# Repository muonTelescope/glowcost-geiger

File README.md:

# gLowCost-geiger

**Simple description:** this is a compact four-wire Geiger module for a Raspberry
Pi. It powers a CTC-5 / STS-5 tube from 3.3 V, generates the tube's high voltage,
and exposes raw TTL pulses plus a future STEMMA QT I²C telemetry interface.
The ATtiny1616 is the production logic device: it counts pulses, serves I2C diagnostics, reads address straps, and reports HV/3V3 telemetry without changing the raw hardware pulse path.

> **Prototype:** the KiCad routing has known DRC clearance errors. The HV design
> is not bench-qualified or approved for fabrication. Use suitable HV procedures.

## Design summary

- Hardware HV oscillator, switch, multiplier, protection, and comparator.
- TTL pulse output plus green 0805 pulse LED with cuttable enable bridge.
- Horizontal CTC-5 / STS-5 tube under two DNP C142864 clips.
- Two STEMMA QT / SparkFun Qwiic connectors in parallel for I²C daisy chaining.
- ATtiny1616 option for pulse counting, HV/3.3 V readback, fault flags, and I²C slave registers.
- Two solder-selectable address pads on leftover MCU GPIOs.
- 120 x 32 x 1.6 mm, two-layer compact PCB.
- Two 1.0 mm routed Edge.Cuts isolation slots split the HV service region.

## STEMMA QT and address selection

STEMMA QT and Qwiic use the same JST-SH 4-pin bus: GND, 3.3 V, SDA, and SCL.
The two connectors are parallel pass-through ports. Enable only one pull-up set on
each bus segment.

Address links are two-pad bridges. Open is logic-high through the ATtiny1616
internal pull-up; bridged is logic-low:

| A1 | A0 | Address |
|---:|---:|---:|
| open | open | `0x2F` |
| open | bridged | `0x30` |
| bridged | open | `0x31` |
| bridged | bridged | `0x32` |

The default `0x2F` is intentionally outside the common addresses called out by
Adafruit; firmware may later store another address. The ATtiny1616 uses UPDI
programming pads (VCC, DATA, GND), not legacy six-wire AVR ISP. UART is exposed
as through-hole debug pads only. All programming and address pads stay on the
low-voltage side.

## Mechanical design

The supplied Littelfuse 102071 drawing and local datasheet agree on the
dimensioned values: 7.6 mm tail pitch, 7.9 mm base width, 10.9 mm height,
R3.2 spring radius, 7.2 mm radius-centre height, 3.6 mm tail extension, and
2.0 +/- 0.1 mm holes. C142864 is DNP at JLC and fitted after assembly.

- [Clip datasheet](kicad/models/C142864-datasheet.pdf)
- [Clip STEP](kicad/models/C142864.step)
- [Clip STL](cad/models/C142864/C142864.stl)
- [FreeCAD source](cad/models/C142864/C142864.FCStd)
- [Annotated comparison](docs/kicad/C142864-annotated-comparison.png)

The STEP is a formed-sheet reconstruction. Bend transitions, stamping,
spring deflection, and tail-hole stamping remain approximate.

## KiCad files

- [Schematic](kicad/glowcost-geiger.kicad_sch)
- [PCB](kicad/glowcost-geiger.kicad_pcb)
- [Project](kicad/glowcost-geiger.kicad_pro)
- [Footprints](kicad/glowcost.pretty)
- [Parts selection](kicad/parts-selection.md) · [net classes](kicad/net-classes.md)
- [ATtiny1616 / STEMMA QT revision specification](kicad/mcu-revision.md)
- [Firmware bring-up and diagnostic tools](firmware/README.md)

The study retains the routed HV prototype and 72 placements. Reroute the known
clearance violations before ordering. The internal slots are fabrication slots,
not copper clearances; confirm JLC's minimum routed-slot width and keep them
clear of clips, traces, and enclosure hardware.

## Render gallery

### Board views

### Assembly and clip

Additional views: [board-top](docs/layout/board-top.png),
[placement](docs/layout/placement.png), [top copper](docs/layout/top-copper.png),
[bottom copper](docs/layout/bottom-copper.png), [courtyards](docs/layout/courtyards.png),
[schematic PNG](docs/kicad/schematic.png), and [schematic PDF](docs/kicad/schematic.pdf).

Renders are for review, not Gerber approval. Generic component bodies are
illustrative; tube seating and HV clearance remain unverified.

Assembly silkscreen now calls out the HV slots, discharge warning, raw pulse,
test points, and tube/clip service area. Install the tube and DNP clips only
after reflow and cleaning; keep conformal coating away from clip contacts,
STEMMA QT contacts, and UPDI/UART pads.

## Electrical and sourcing notes

The tube is biased near 400 V. The protected HV divider scales the sense node to
0–3.3 V for the MCU ADC; never connect an MCU pin directly to the tube supply.
Keep HV service nets away from STEMMA QT and Pi wiring.

ATtiny1616-MNR (LCSC C507118) is the preferred MCU: QFN-20, 3 x 3 mm, 16 KB
Flash, 2 KB SRAM, 10-bit ADC, I²C/TWI, timers, Event System, and UPDI. Current
LCSC pricing is typically about $0.90–1.10. See [cost-parts.json](docs/cost-parts.json)
and [review-bom.csv](docs/review-bom.csv) for the cost study.

## SPICE and measured-design findings

The simulations are behavioral planning models, not a substitute for a loaded
tube test. Regenerated outputs are kept here:

| Plot | What it shows |
|---|---|
|  | HV rise and startup time |
|  | HV regulation across modeled loads |
|  | Divider and clamp behavior |
|  | Comparator/TTL pulse shape |
|  | Synthetic pulse-pair response |
|  | Dead-time and rate-loss limits |

Current planning values are approximately 399 V mean HV, 7 V peak-to-peak
ripple, 37–39 ms startup, 190 µs reference dead time, and about 2.5 mA
converter input current in the nominal model. These values still require bench
validation with the actual tube and transformer.

The rate model reaches 1% loss near 40–53 cps depending on the selected dead
time, and the nominal 400 V / 10% loss point is about 2.55 µSv/min using the
uncalibrated 2.9 cps per µSv/h conversion. Counts remain the primary output;
the dose estimate is approximate.

## Findings to resolve before fabrication

- The KiCad prototype still has known DRC clearance violations; resolve these before fabrication.
- The ATtiny1616, two STEMMA QT connectors, address bridges, and UART/UPDI pads
  are specified but not yet integrated into the native schematic/PCB release.
- The 1 mm HV slots are present as Edge.Cuts and must be checked against JLC's
  routed-slot capability and the final Gerbers.
- The C142864 STEP is a reconstructed formed-sheet model; stamped tail holes and
  spring deflection are not production-qualified.
- HV creepage, tube seating, conformal-coating boundaries, and loaded current
  remain open hardware checks.

The deterministic review report is [jev-review.json](docs/kicad/jev-review.json).
Jev may rank legal routing candidates, but it does not replace KiCad DRC,
clearance calculations, or human HV review.

## Reproduce outputs

```sh
npm run build:kicad
PYTHONPATH=/Applications/FreeCAD.app/Contents/Resources/lib \
  /Applications/FreeCAD.app/Contents/Resources/bin/python scripts/generate_clip_model.py
blender --background --python scripts/render_clip_model.py
blender --background --python scripts/render_assembly.py
kicad-cli pcb render -o docs/renders/board/top.png \
  kicad/glowcost-geiger.kicad_pcb --side top --quality high
```

Before fabrication: integrate and lock the ATtiny schematic/layout, define the
I²C register map, verify address links, reroute DRC errors, confirm HV creepage,
and test the loaded tube assembly.

## Optional Jev semantic review

KiCad DRC, geometry checks, and clearance calculations remain deterministic.
Jev is optional for higher-level review such as ranking decoupler placement,
flagging a switcher near sensitive analog, or prioritizing silkscreen and
assembly risks. It should receive structured board facts, never replace DRC,
and never receive API keys or private files in the repository.

To enable a local TypeSafe integration, install the TypeSafe SDK in your own
environment and provide the key only through an environment variable:

```sh
export TYPESAFE_API_KEY='paste-a-new-key-here'
```

Do not commit the key, put it in this README, or paste it into issue reports.
The repository currently documents the semantic-review approach but does not
call Jev during the KiCad build. Run the review explicitly with:

```sh
source .venv/bin/activate
python scripts/jev_pcb_review.py
```

It writes `docs/kicad/jev-review.json`. With `TYPESAFE_API_KEY` set, Jev ranks
the legal trace-width candidates; without a key, the deterministic rule gate
still produces a useful report. Jev never edits the PCB and cannot override
KiCad DRC, minimum widths, HV creepage, or the 1 mm isolation slots.

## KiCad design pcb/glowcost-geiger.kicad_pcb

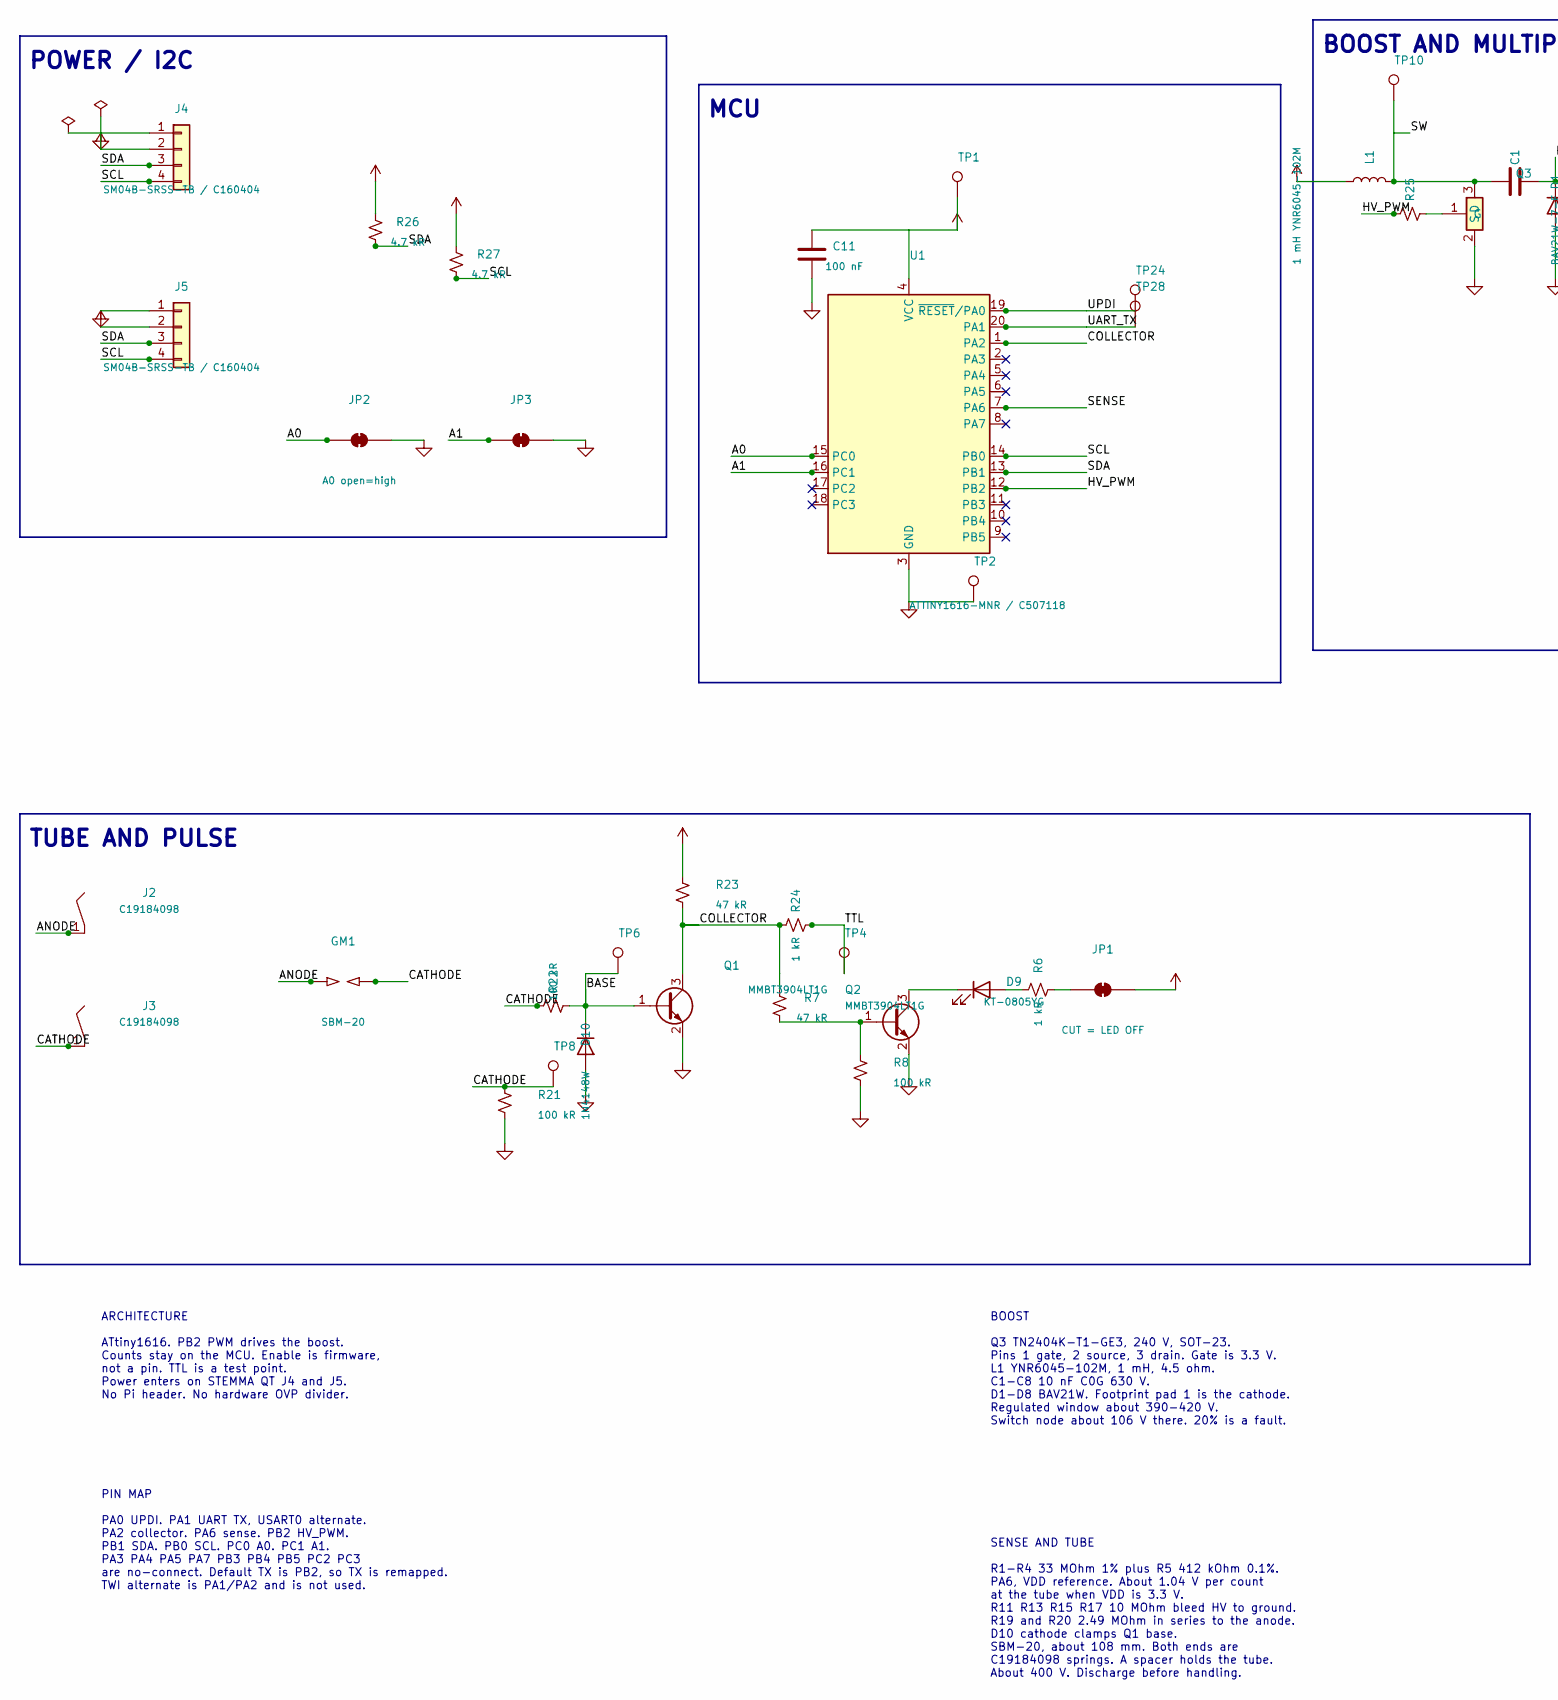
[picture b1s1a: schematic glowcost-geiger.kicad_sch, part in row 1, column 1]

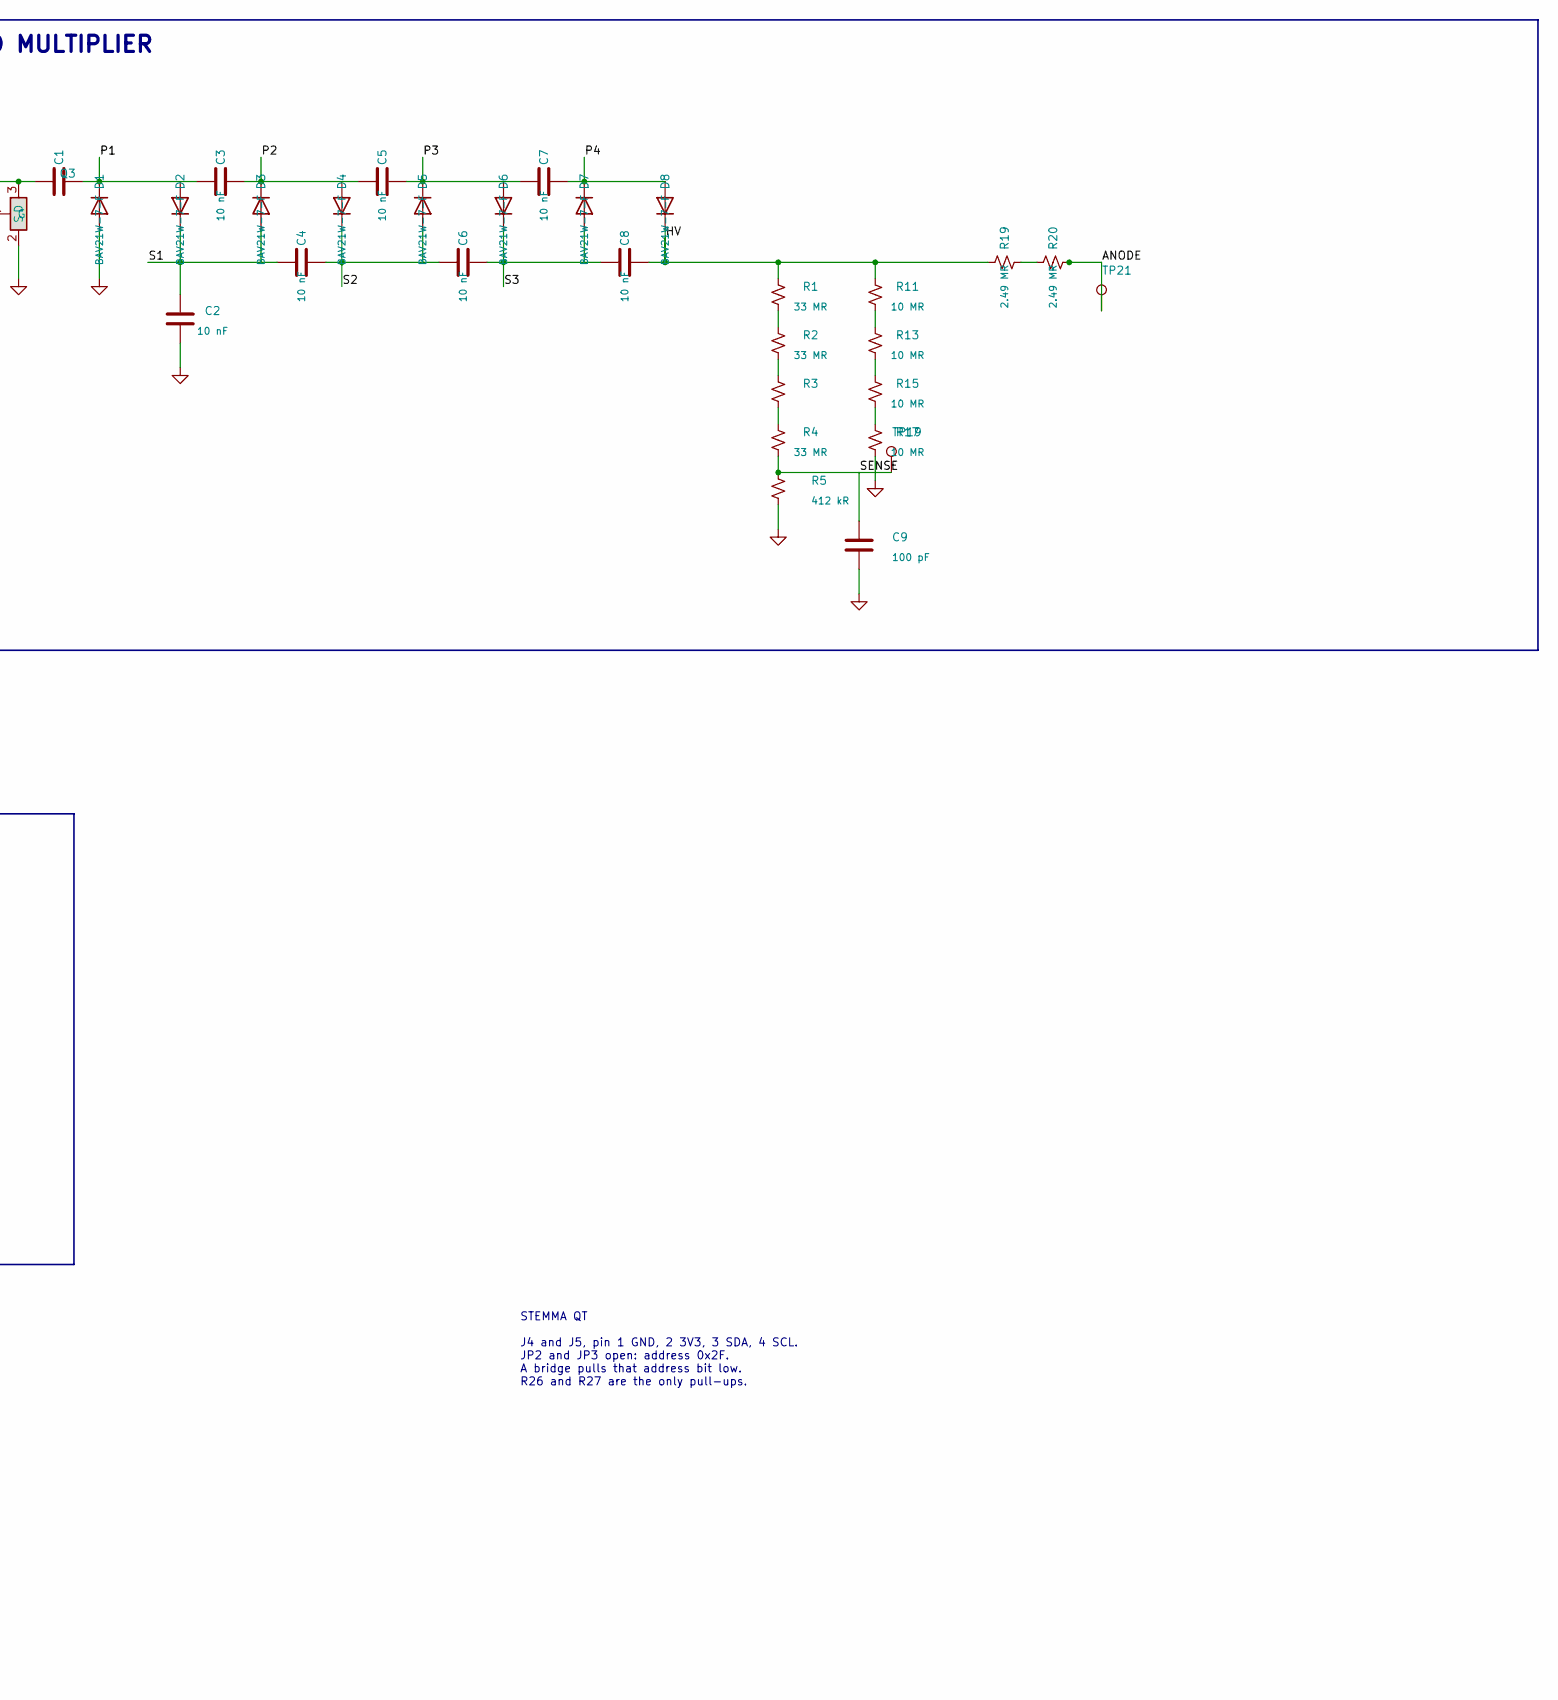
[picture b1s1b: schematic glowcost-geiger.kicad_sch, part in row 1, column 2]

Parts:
C1: 10 nF; C1; MPN C3216C0G2J103JT000N; LCSC C342714
C2: 10 nF; C2; MPN C3216C0G2J103JT000N; LCSC C342714
C3: 10 nF; C3; MPN C3216C0G2J103JT000N; LCSC C342714
C4: 10 nF; C4; MPN C3216C0G2J103JT000N; LCSC C342714
C5: 10 nF; C5; MPN C3216C0G2J103JT000N; LCSC C342714
C6: 10 nF; C6; MPN C3216C0G2J103JT000N; LCSC C342714
C7: 10 nF; C7; MPN C3216C0G2J103JT000N; LCSC C342714
C8: 10 nF; C8; MPN C3216C0G2J103JT000N; LCSC C342714
C9: 100 pF; C9; MPN CL10C101JB8NNNC; LCSC C14858
C11: 100 nF; C_0603_1608Metric; MPN CL10B104KB8NNNC; LCSC C1591
D1: BAV21W-7-F; D1; MPN BAV21W-7-F; LCSC C155214
D2: BAV21W-7-F; D2; MPN BAV21W-7-F; LCSC C155214
D3: BAV21W-7-F; D3; MPN BAV21W-7-F; LCSC C155214
D4: BAV21W-7-F; D4; MPN BAV21W-7-F; LCSC C155214
D5: BAV21W-7-F; D5; MPN BAV21W-7-F; LCSC C155214
D6: BAV21W-7-F; D6; MPN BAV21W-7-F; LCSC C155214
D7: BAV21W-7-F; D7; MPN BAV21W-7-F; LCSC C155214
D8: BAV21W-7-F; D8; MPN BAV21W-7-F; LCSC C155214
D9: KT-0805YG; D_LED; MPN KT-0805YG; LCSC C2292
D10: 1N4148W; D_NEG; MPN 1N4148W; LCSC C81598
GM1: SBM-20
J2, J3: C19184098; MY-AA-03; MPN MY-AA-03; LCSC C19184098
J4, J5: SM04B-SRSS-TB / C160404; JST_SH_SM04B-SRSS-TB_1x04-1MP_P1.00mm_Horizontal; MPN SM04B-SRSS-TB(LF)(SN); LCSC C160404
JP1: CUT = LED OFF; SJ_LED
JP2: A0 open=high; SJ_LED
JP3: A1 open=high; SJ_LED
L1: 1 mH YNR6045-102M; L_6.3x6.3_H3; MPN YNR6045-102M; LCSC C497845
Q1: MMBT3904LT1G; Q1; MPN MMBT3904LT1G; LCSC C81464
Q2: MMBT3904LT1G; Q_LED; MPN MMBT3904LT1G; LCSC C81464
Q3: TN2404K / C468011; SOT-23; MPN TN2404K-T1-GE3; LCSC C468011
R1: 33 MR; R1; MPN FRG2512F3305TS; LCSC C5126202
R2: 33 MR; R2; MPN FRG2512F3305TS; LCSC C5126202
R3: 33 MR; R3; MPN FRG2512F3305TS; LCSC C5126202
R4: 33 MR; R4; MPN FRG2512F3305TS; LCSC C5126202
R5: 412 kR; R5; MPN PTFR0603B412KP9; LCSC C47115896
R6: 1 kR; R_LED; MPN 0603WAF1001T5E; LCSC C21190
R7: 47 kR; R_LB; MPN 0603WAF4702T5E; LCSC C25819
R8: 100 kR; R_LPD; MPN 0603WAF1003T5E; LCSC C25803
R11: 10 MR; R_BL1; MPN 1206W4F1005T5E; LCSC C26119
R13: 10 MR; R_BL2; MPN 1206W4F1005T5E; LCSC C26119
R15: 10 MR; R_BL3; MPN 1206W4F1005T5E; LCSC C26119
R17: 10 MR; R_BL4; MPN 1206W4F1005T5E; LCSC C26119
R19: 2.49 MR; R_A1; MPN CRHV1206AF2M49FKEF
R20: 2.49 MR; R_A2; MPN CRHV1206AF2M49FKEF
R21: 100 kR; R_K; MPN 0603WAF1003T5E; LCSC C25803
R22: 100 kR; R_PROTECT; MPN 0603WAF1003T5E; LCSC C25803
R23: 47 kR; R_COL; MPN 0603WAF4702T5E; LCSC C25819
R24: 1 kR; R_OUT; MPN 0603WAF1001T5E; LCSC C21190
R25: 220 R; R_OUT; MPN 0603WAF2200T5E; LCSC C17577
R26, R27: 4.7 kR; R_OUT; MPN 0603WAF4701T5E; LCSC C23162
TP1: V3V3; TP1
TP2: GND; TP2
TP4: TTL; TP4
TP6: BASE; TP6
TP8: CATHODE; TP8
TP10: SW; TP10
TP19: SENSE; TP19
TP21: ANODE; TP21
TP24: UPDI; TP1
TP28: UART_TX; TP1
U1: ATTINY1616-MNR / C507118; VQFN-20-1EP_3x3mm_P0.4mm_EP1.7x1.7mm; MPN ATTINY1616-MNR; LCSC C507118

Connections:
/A0: JP2.1 (A), U1.15 (PC0)
/A1: JP3.1 (A), U1.16 (PC1)
/ANODE: GM1.1, J2.1, R20.2, TP21.1
/BASE: D10.1 (K), Q1.1 (B), R22.2, TP6.1
/CATHODE: GM1.2, J3.1, R21.1, R22.1, TP8.1
/COLLECTOR: Q1.3 (C), R7.1, R23.2, R24.1, U1.1 (PA2)
/HV: C8.2, D8.1 (K), R1.1, R11.1, R19.1
/HV_PWM: R25.1, U1.12 (PB2)
/P1: C1.2, C3.1, D1.1 (K), D2.2 (A)
/P2: C3.2, C5.1, D3.1 (K), D4.2 (A)
/P3: C5.2, C7.1, D5.1 (K), D6.2 (A)
/P4: C7.2, D7.1 (K), D8.2 (A)
/S1: C2.2, C4.1, D2.1 (K), D3.2 (A)
/S2: C4.2, C6.1, D4.1 (K), D5.2 (A)
/S3: C6.2, C8.1, D6.1 (K), D7.2 (A)
/SCL: J4.4, J5.4, R27.2, U1.14 (PB0)
/SDA: J4.3, J5.3, R26.2, U1.13 (PB1)
/SENSE: C9.1, R4.2, R5.1, TP19.1, U1.7 (PA6)
/SW: C1.1, L1.2, Q3.3 (D), TP10.1
/TTL: R24.2, TP4.1
/UART_TX: TP28.1, U1.20 (PA1)
/UPDI: TP24.1, U1.19 (~RESET/PA0)
unnamed: D9.2 (A), R6.1
unnamed: D9.1 (K), Q2.3 (C)
unnamed: JP1.2 (B), R6.2
unnamed: Q2.1 (B), R7.2, R8.1
unnamed: Q3.1 (G), R25.2
unnamed: R1.2, R2.1
unnamed: R2.2, R3.1
unnamed: R3.2, R4.1
unnamed: R11.2, R13.1
unnamed: R13.2, R15.1
unnamed: R15.2, R17.1
unnamed: R19.2, R20.1

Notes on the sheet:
ARCHITECTURE ATtiny1616. PB2 PWM drives the boost. Counts stay on the MCU. Enable is firmware, not a pin. TTL is a test point. Power enters on STEMMA QT J4 and J5. No Pi header. No hardware OVP divider.
PIN MAP PA0 UPDI. PA1 UART TX, USART0 alternate. PA2 collector. PA6 sense. PB2 HV_PWM. PB1 SDA. PB0 SCL. PC0 A0. PC1 A1. PA3 PA4 PA5 PA7 PB3 PB4 PB5 PC2 PC3 are no-connect. Default TX is PB2, so TX is remapped. TWI alternate is PA1/PA2 and is not used.
BOOST Q3 TN2404K-T1-GE3, 240 V, SOT-23. Pins 1 gate, 2 source, 3 drain. Gate is 3.3 V. L1 YNR6045-102M, 1 mH, 4.5 ohm. C1-C8 10 nF C0G 630 V. D1-D8 BAV21W. Footprint pad 1 is the cathode. Regulated window about 390-420 V. Switch node about 106 V there. 20% is a fault.
SENSE AND TUBE R1-R4 33 MOhm 1% plus R5 412 kOhm 0.1%. PA6, VDD reference. About 1.04 V per count at the tube when VDD is 3.3 V. R11 R13 R15 R17 10 MOhm bleed HV to ground. R19 and R20 2.49 MOhm in series to the anode. D10 cathode clamps Q1 base. SBM-20, about 108 mm. Both ends are C19184098 spring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
STEMMA QT J4 and J5, pin 1 GND, 2 3V3, 3 SDA, 4 SCL. JP2 and JP3 open: address 0x2F. A bridge pulls that address bit low. R26 and R27 are the only pull-ups.
POWER / I2C
MCU
BOOST AND MULTIPLIER
TUBE AND PULSE

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
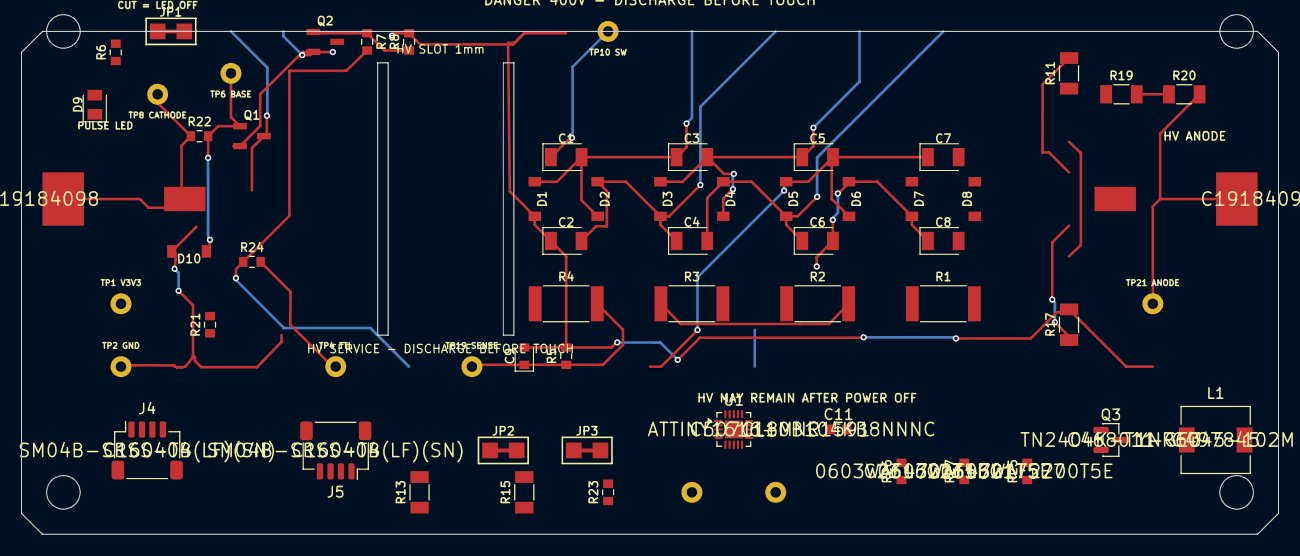
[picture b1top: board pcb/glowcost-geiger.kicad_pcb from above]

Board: 2 copper layers, 120.0 x 48.0 mm, 68 parts (0 on the bottom side), 36 nets.

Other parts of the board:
H1: MountingHole_3.2mm; H1
H2: MountingHole_3.2mm; H2
H3: MountingHole_3.2mm; H3
H4: MountingHole_3.2mm; H4
MECH1: Tube_Assembly_Model

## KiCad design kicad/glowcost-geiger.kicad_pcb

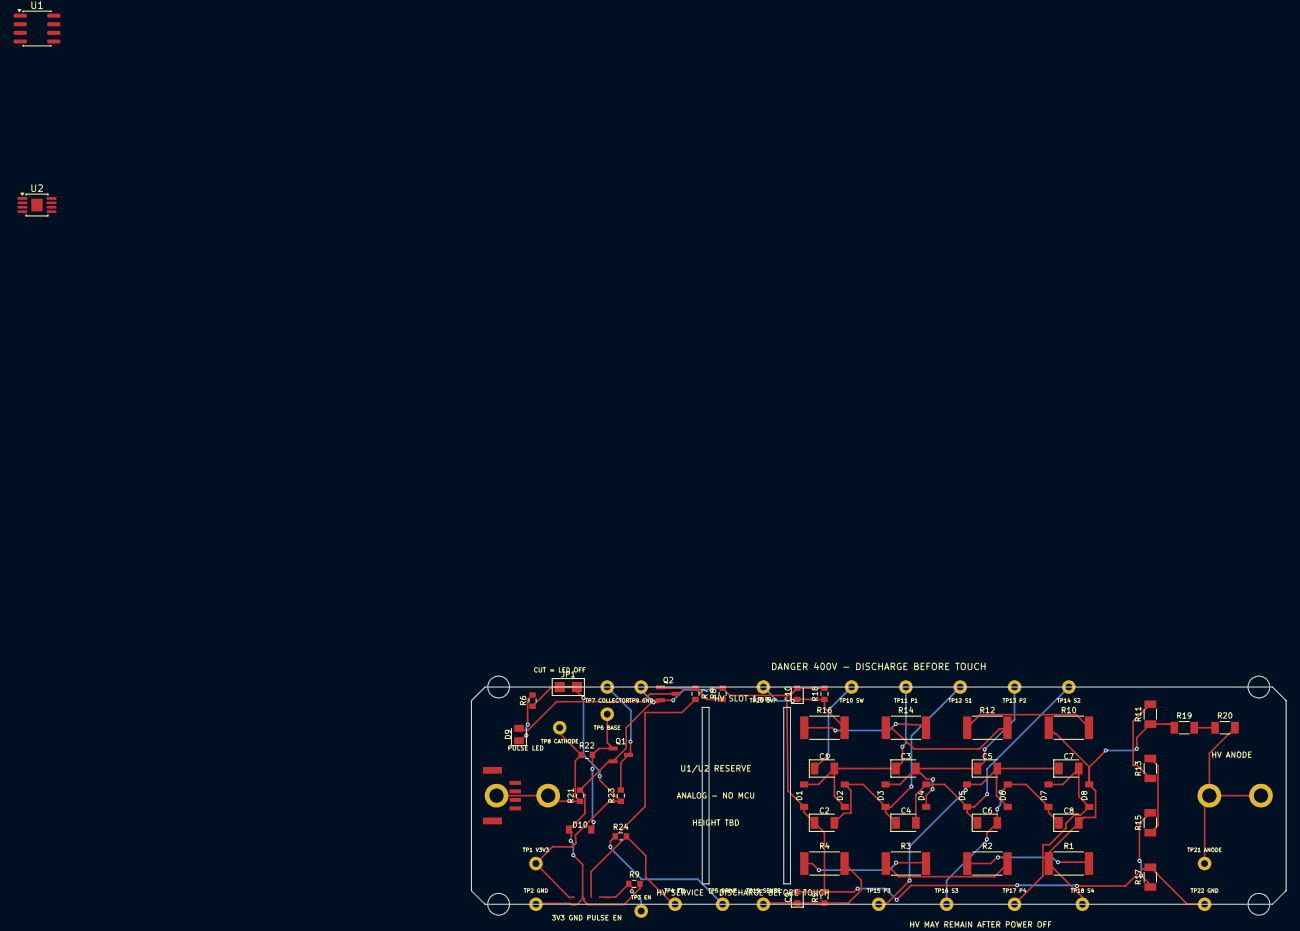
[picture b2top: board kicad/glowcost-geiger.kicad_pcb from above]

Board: 2 copper layers, 120.0 x 32.0 mm, 79 parts (0 on the bottom side), 34 nets.

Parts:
C1: 10 nF; C1
C2: 10 nF; C2
C3: 10 nF; C3
C4: 10 nF; C4
C5: 10 nF; C5
C6: 10 nF; C6
C7: 10 nF; C7
C8: 10 nF; C8
C9: 100 pF; C9
C10: 10 pF; C_OV
D1: BAV21W-7-F; D1
D2: BAV21W-7-F; D2
D3: BAV21W-7-F; D3
D4: BAV21W-7-F; D4
D5: BAV21W-7-F; D5
D6: BAV21W-7-F; D6
D7: BAV21W-7-F; D7
D8: BAV21W-7-F; D8
D9: KT-0805YG; D_LED
D10: 1N4148W; D_NEG
H1: MountingHole_3.2mm; H1
H2: MountingHole_3.2mm; H2
H3: MountingHole_3.2mm; H3
H4: MountingHole_3.2mm; H4
J1: JST GH 4-pin; J1
J2: C142864 DNP; J2
J3: C142864 DNP; J3
JP1: CUT = LED OFF; SJ_LED
MECH1: Tube_Assembly_Model
Q1: MMBT3904LT1G; Q1
Q2: MMBT3904LT1G; Q_LED
R1: 33 MR; R1
R2: 33 MR; R2
R3: 33 MR; R3
R4: 33 MR; R4
R5: 412 kR; R5
R6: 1 kR; R_LED
R7: 47 kR; R_LB
R8: 100 kR; R_LPD
R9: 100 kR; R_EN
R10: 33 MR; R_OV1
R11: 10 MR; R_BL1
R12: 33 MR; R_OV2
R13: 10 MR; R_BL2
R14: 33 MR; R_OV3
R15: 10 MR; R_BL3
R16: 33 MR; R_OV4
R17: 10 MR; R_BL4
R18: 402 kR; R_OVBOT
R19: 2.49 MR; R_A1
R20: 2.49 MR; R_A2
R21: 100 kR; R_K
R22: 100 kR; R_PROTECT
R23: 47 kR; R_COL
R24: 1 kR; R_OUT
TP1: V3V3; TP1
TP2: GND; TP2
TP3: EN; TP3
TP4: TTL; TP4
TP5: DRIVE; TP5
TP6: BASE; TP6
TP7: COLLECTOR; TP7
TP8: CATHODE; TP8
TP9: GND; TP9
TP10: SW; TP10
TP11: P1; TP11
TP12: S1; TP12
TP13: P2; TP13
TP14: S2; TP14
TP15: P3; TP15
TP16: S3; TP16
TP17: P4; TP17
TP18: S4; TP18
TP19: SENSE; TP19
TP20: OVP; TP20
TP21: ANODE; TP21
TP22: GND; TP22
U1: TLC555IDR; U1
U2: MCP6562T-E/MS; U2

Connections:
/ANODE: J2.1, J2.2, R20.2, TP21.1
/ANODE_MID: R19.2, R20.1
/BASE: D10.2, Q1.1, R22.2, TP6.1
/BL1: R11.2, R13.1
/BL2: R13.2, R15.1
/BL3: R15.2, R17.1
/CATHODE: J3.1, J3.2, R21.1, R22.1, TP8.1
/COLLECTOR: Q1.3, R23.2, TP7.1
/DIV1: R1.2, R2.1
/DIV2: R2.2, R3.1
/DIV3: R3.2, R4.1
/DRIVE: R7.1, R24.1, TP5.1
/EN: J1.4, R9.1, TP3.1
/LED_A: D9.1, R6.2
/LED_BASE: Q2.1, R7.2, R8.1
/LED_K: D9.2, Q2.3
/LED_SUPPLY: JP1.2, R6.1
/OV1: R10.2, R12.1
/OV2: R12.2, R14.1
/OV3: R14.2, R16.1
/OVP: C10.1, R16.2, R18.1, TP20.1
/P1: C1.2, C3.1, D1.2, D2.1, TP11.1
/P2: C3.2, C5.1, D3.2, D4.1, TP13.1
/P3: C5.2, C7.1, D5.2, D6.1, TP15.1
/P4: C7.2, D7.2, D8.1, TP17.1
/S1: C2.2, C4.1, D2.2, D3.1, TP12.1
/S2: C4.2, C6.1, D4.2, D5.1, TP14.1
/S3: C6.2, C8.1, D6.2, D7.1, TP16.1
/S4: C8.2, D8.2, R1.1, R10.1, R11.1, R19.1, TP18.1
/SENSE: C9.1, R4.2, R5.1, TP19.1
/SW: C1.1, TP10.1
/TTL: J1.3, R24.2, TP4.1
GND: C2.1, C9.2, C10.2, D1.1, D10.1, J1.2, Q1.2, Q2.2, R5.2, R8.2, R9.2, R17.2, R18.2, R21.2, TP2.1, TP9.1, TP22.1
V3V3: J1.1, JP1.1, R23.1, TP1.1

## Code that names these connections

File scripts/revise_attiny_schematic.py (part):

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    sch = new_sch
    print("Removed:", removed)

    # Rename DRIVE labels → COLLECTOR so TTL path ties to pulse node without U2
    drive_renames = 0
    for item in sch:
        if isinstance(item, list) and item and item[0] == "label" and item[1] == "DRIVE":
            item[1] = "COLLECTOR"
            drive_renames += 1
    print("DRIVE→COLLECTOR labels:", drive_renames)

    # Placement origin for new MCU block (reuse old U1 area)
    ox, oy = 70.0, 45.0
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    # Title note
    additions.append(text_note(
        "ATtiny-only revision: MCU PWM drives boost; pulse count + I2C + ADC.\\n"
        "USART0 must use alternate TX=PA1 (PB2 is HV_PWM). Default I2C addr 0x2F.",
        ox - 10, oy - 25, 1.1))
    additions.append(rect(ox - 15, oy - 30, ox + 95, oy + 55))

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    # Pin coordinates for ATtiny406-M style symbol (from stock layout)
    # Approximate from typical KiCad tinyAVR VQFN-20 symbol — use labels near chip with short wires
    # We'll place hierarchical-style local labels around the chip body based on known pin sides:
    # From ATtiny406-M: left PA2,PA3,GND,VCC,PA4..; right side etc.
    # Safer: place labels with net names and short stubs using documented pin positions from SVG export after first place.
    # For v1: put floating labels + wires to a connector strip of labels at known offsets.

    # Net labels around MCU (label-only wiring to existing named nets)
    mcu_labels = [
        # leftish / function
        ("COLLECTOR", ox + 10, oy + 5),   # PA2 pulse
        ("SDA", ox + 10, oy + 15),
        ("SCL", ox + 10, oy + 20),
        ("SENSE", ox + 10, oy + 25),
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
    # Explicit pin-associated labels via junction notes (text)
    additions.append(text_note(
        "U1 map: PA2=COLLECTOR PA4=SDA PA5=SCL PA6=SENSE PA7=V3V3_SENSE\\n"
        "PB0=A0 PB1=A1 PB2=HV_PWM PB3=EN PA0=UPDI PA1=UART_TX EP=GND",
        ox - 10, oy + 45, 1.0))

    # Boost: L1 + Q_HV + R_GATE near existing SW net
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        footprint="Inductor_SMD:L_1210_3225Metric",
        lcsc="C2041861", mpn="B82442T1105K050",
    ))
    additions.append(label("V3V3", bx + 10, by - 5.08))
    additions.append(label("SW", bx + 10, by + 5.08))
    additions.append(wire(bx + 10, by - 3.81, bx + 10, by - 5.08))
    additions.append(wire(bx + 10, by + 3.81, bx + 10, by + 5.08))
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        footprint="glowcost:R1",  # reuse 0603-ish from project if present
        lcsc="C17577", mpn="0603WAF2200T5E",
    ))
    additions.append(label("HV_PWM", bx + 15, by + 5))
    additions.append(label("SW", bx + 35, by - 2))
    additions.append(label("GND", bx + 35, by + 12))
    additions.append(text_note("Q3:1=G 2=S 3=D  R25 gate", bx + 15, by + 18, 1.0))
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            lcsc="C160404", mpn="SM04B-SRSS-TB(LF)(SN)",
        ))
        additions.append(label("GND", x - 8, sy + 2.54))
        additions.append(label("V3V3", x - 8, sy + 0))
        additions.append(label("SDA", x - 8, sy - 2.54))
        additions.append(label("SCL", x - 8, sy - 5.08))
        # wires from connector pins (Conn_01x04 pins on left at -5.08)
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        "Glowcost:R_Small_US", "R27", "4.7 kR",
        sx + 35, sy - 30, 0, ["1", "2"], footprint="glowcost:R1", lcsc="C23162", mpn="0603WAF4701T5E",
    ))
    additions.append(label("V3V3", sx + 20, sy - 36))
    additions.append(label("SDA", sx + 20, sy - 24))
    additions.append(label("V3V3", sx + 35, sy - 36))
    additions.append(label("SCL", sx + 35, sy - 24))
    additions.append(text_note("R26/R27: populate only one bus segment", sx + 45, sy - 30, 1.0))

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        "Glowcost:C", "C11", "100 nF",
        ox + 55, oy - 15, 0, ["1", "2"], footprint="glowcost:C1", lcsc="C14663", mpn="CL10B104KB8NNNC",
    ))
    additions.append(label("V3V3", ox + 55, oy - 20))
    additions.append(label("GND", ox + 55, oy - 10))

    # 3V3 sense divider (simple)
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        "Glowcost:R_Small_US", "R29", "10 kR",
        ox + 75, oy - 5, 0, ["1", "2"], footprint="glowcost:R1",
    ))
    additions.append(label("V3V3", ox + 75, oy - 20))
    additions.append(label("V3V3_SENSE", ox + 85, oy - 10))
    additions.append(label("GND", ox + 75, oy + 2))

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                if num and str(num[1]) == "1" and val is not None:
                    val[1] = "ATtiny-only: MCU PWM boost + pulse/I2C; STEMMA J4/J5; no 555/MCP6562"
                if num and str(num[1]) == "2" and val is not None:
                    val[1] = "Wire U1 pins to labels in Eeschema; verify PORTMUX UART alt=PA1"

    # Append additions before sheet_instances / embedded if any
    insert_at = len(sch)
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
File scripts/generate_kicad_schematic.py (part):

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 # top common sense rail / ground bottom rail
 a=pins[prefix+'4']['2'];b=pins[bottom]['1'];c=pins[cap]['1']
 wire(a,(b[0],a[1]));wire((b[0],a[1]),b);wire((b[0],a[1]),(c[0],a[1]));wire((c[0],a[1]),c)
 label('SENSE' if prefix=='R' else 'OVP',(b[0],a[1]))
 used.update([(prefix+'4','2'),(bottom,'1'),(cap,'1')])
 note('399.16 V = 1.242 x (132M + 412k) / 412k\n3.02 uA at 400 V; C9 time constant ~41 us.' if prefix=='R' else '409.06 V = 1.242 x (132M + 402k) / 402k\nSeparate reference required; latch / inhibit driver.',x-8,163,1.2)
for i in range(4):put('R_BL'+str(i+1),294.64+i*30.48,137.16,90)
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wire((114.3,200.66),pins['R_K']['1']);used.add(('R_K','1'))
items.append(['junction',['at',114.3,200.66],['diameter',0],['color',0,0,0,0],['uuid',uid('cathode-junction')]])
wire(pins['R_PROTECT']['2'],(147.32,200.66));wire((147.32,200.66),(147.32,210.82));wire((147.32,210.82),pins['Q1']['1'])
label('BASE',(147.32,210.82));used.update([('R_PROTECT','2'),('Q1','1')])
put('J2',30.48,231.14);put('J3',68.58,231.14)
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# LED default bridge, resistor, LED and buffered sink.
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 if ref.startswith('#'):continue
 for n in pins[ref]:
  if (ref,n) not in used:terminal(ref,n,2.54 if ref.startswith('TP') else 5.08)
put('#FLG01',71.12,30.48,value='PWR_FLAG');label('V3V3',(71.12,30.48))
put('#FLG02',96.52,30.48,value='PWR_FLAG');label('GND',(96.52,30.48))
# All atoms are made explicit, with strings only where KiCad expects text.
# Parse generated text via a helper to normalize bare enum atoms below.
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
